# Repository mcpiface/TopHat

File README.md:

# TopHat

Pi Top "Hat" to provide blade style power connectivity through from a back plane, with the addition of McPiFace I2C connections, front panel LED connection and some additional functionality.

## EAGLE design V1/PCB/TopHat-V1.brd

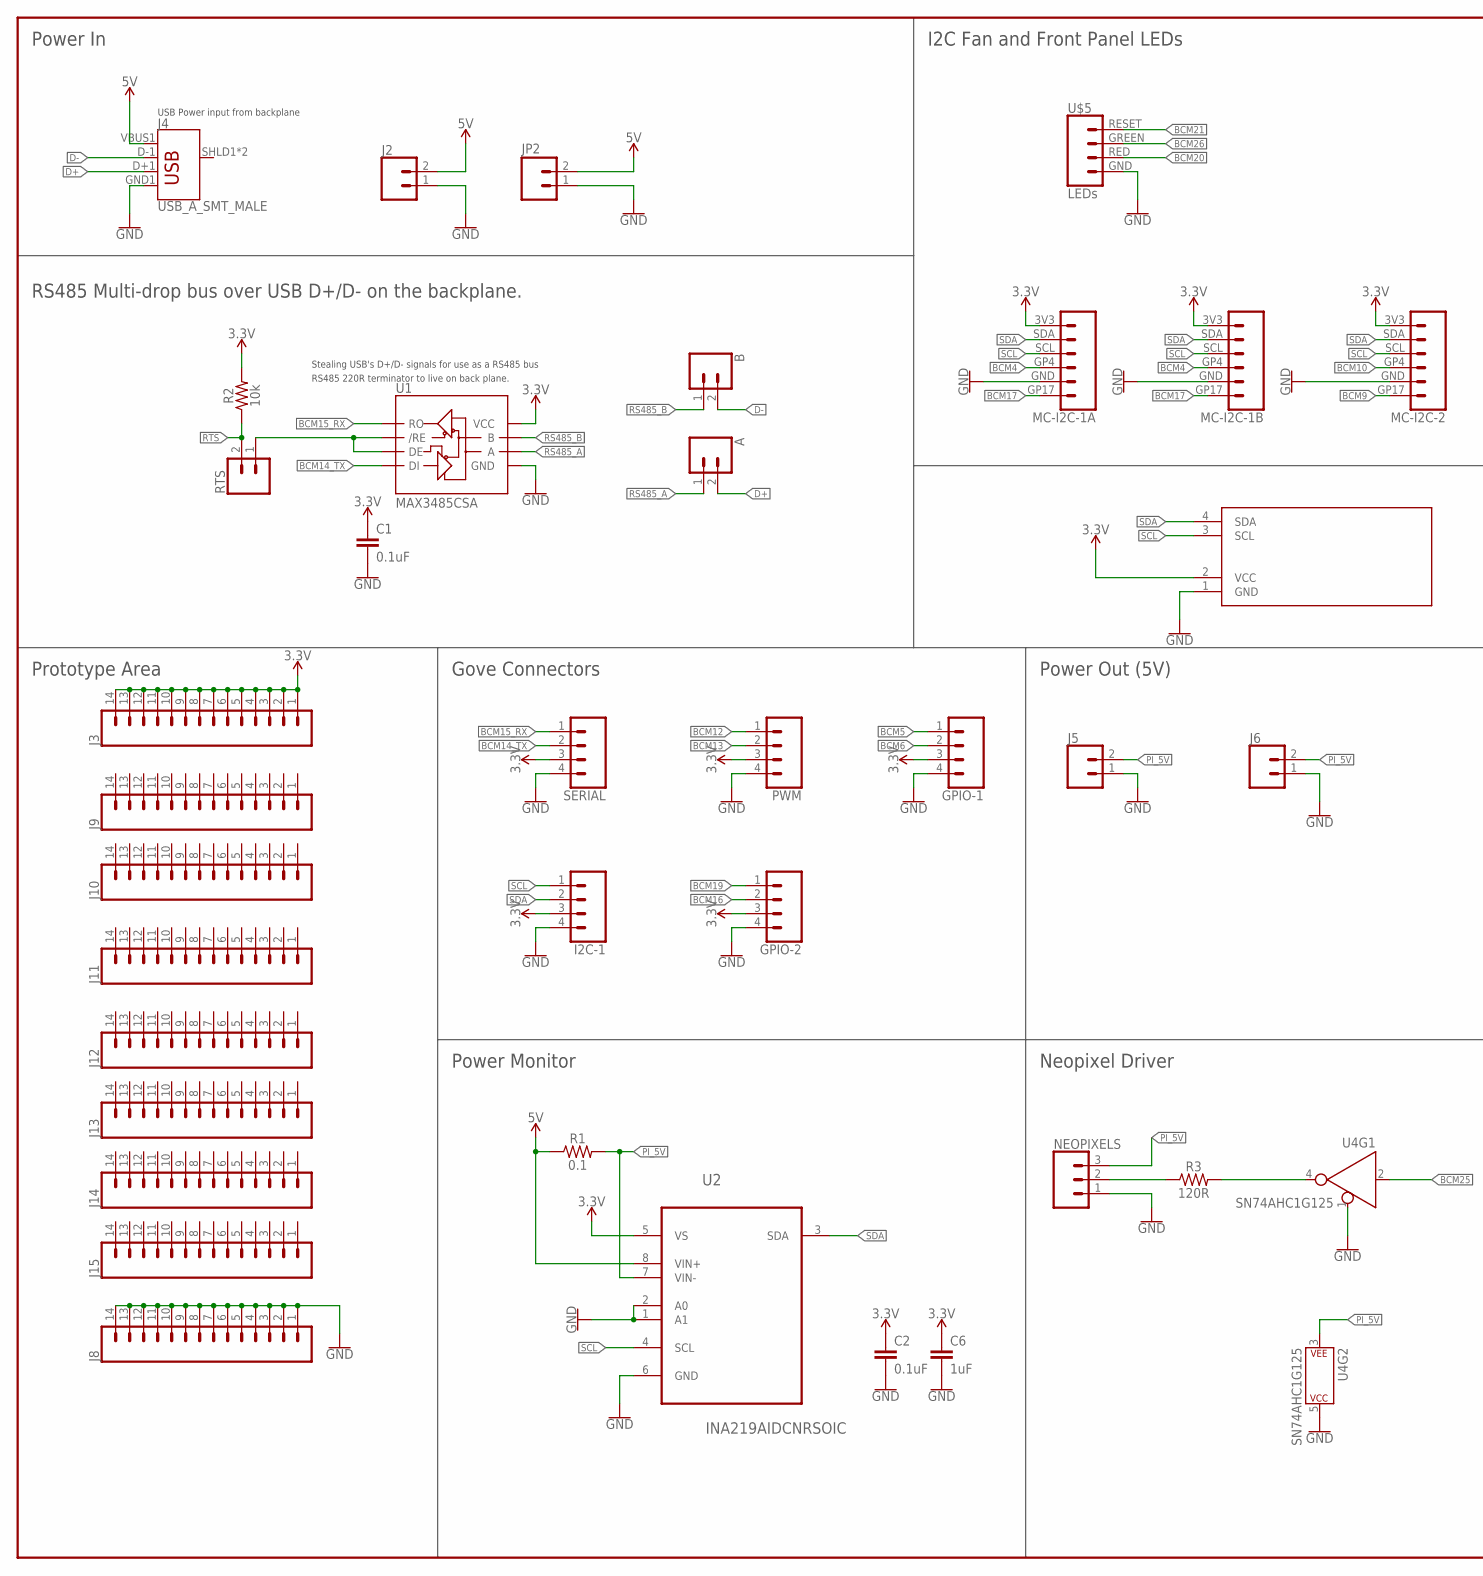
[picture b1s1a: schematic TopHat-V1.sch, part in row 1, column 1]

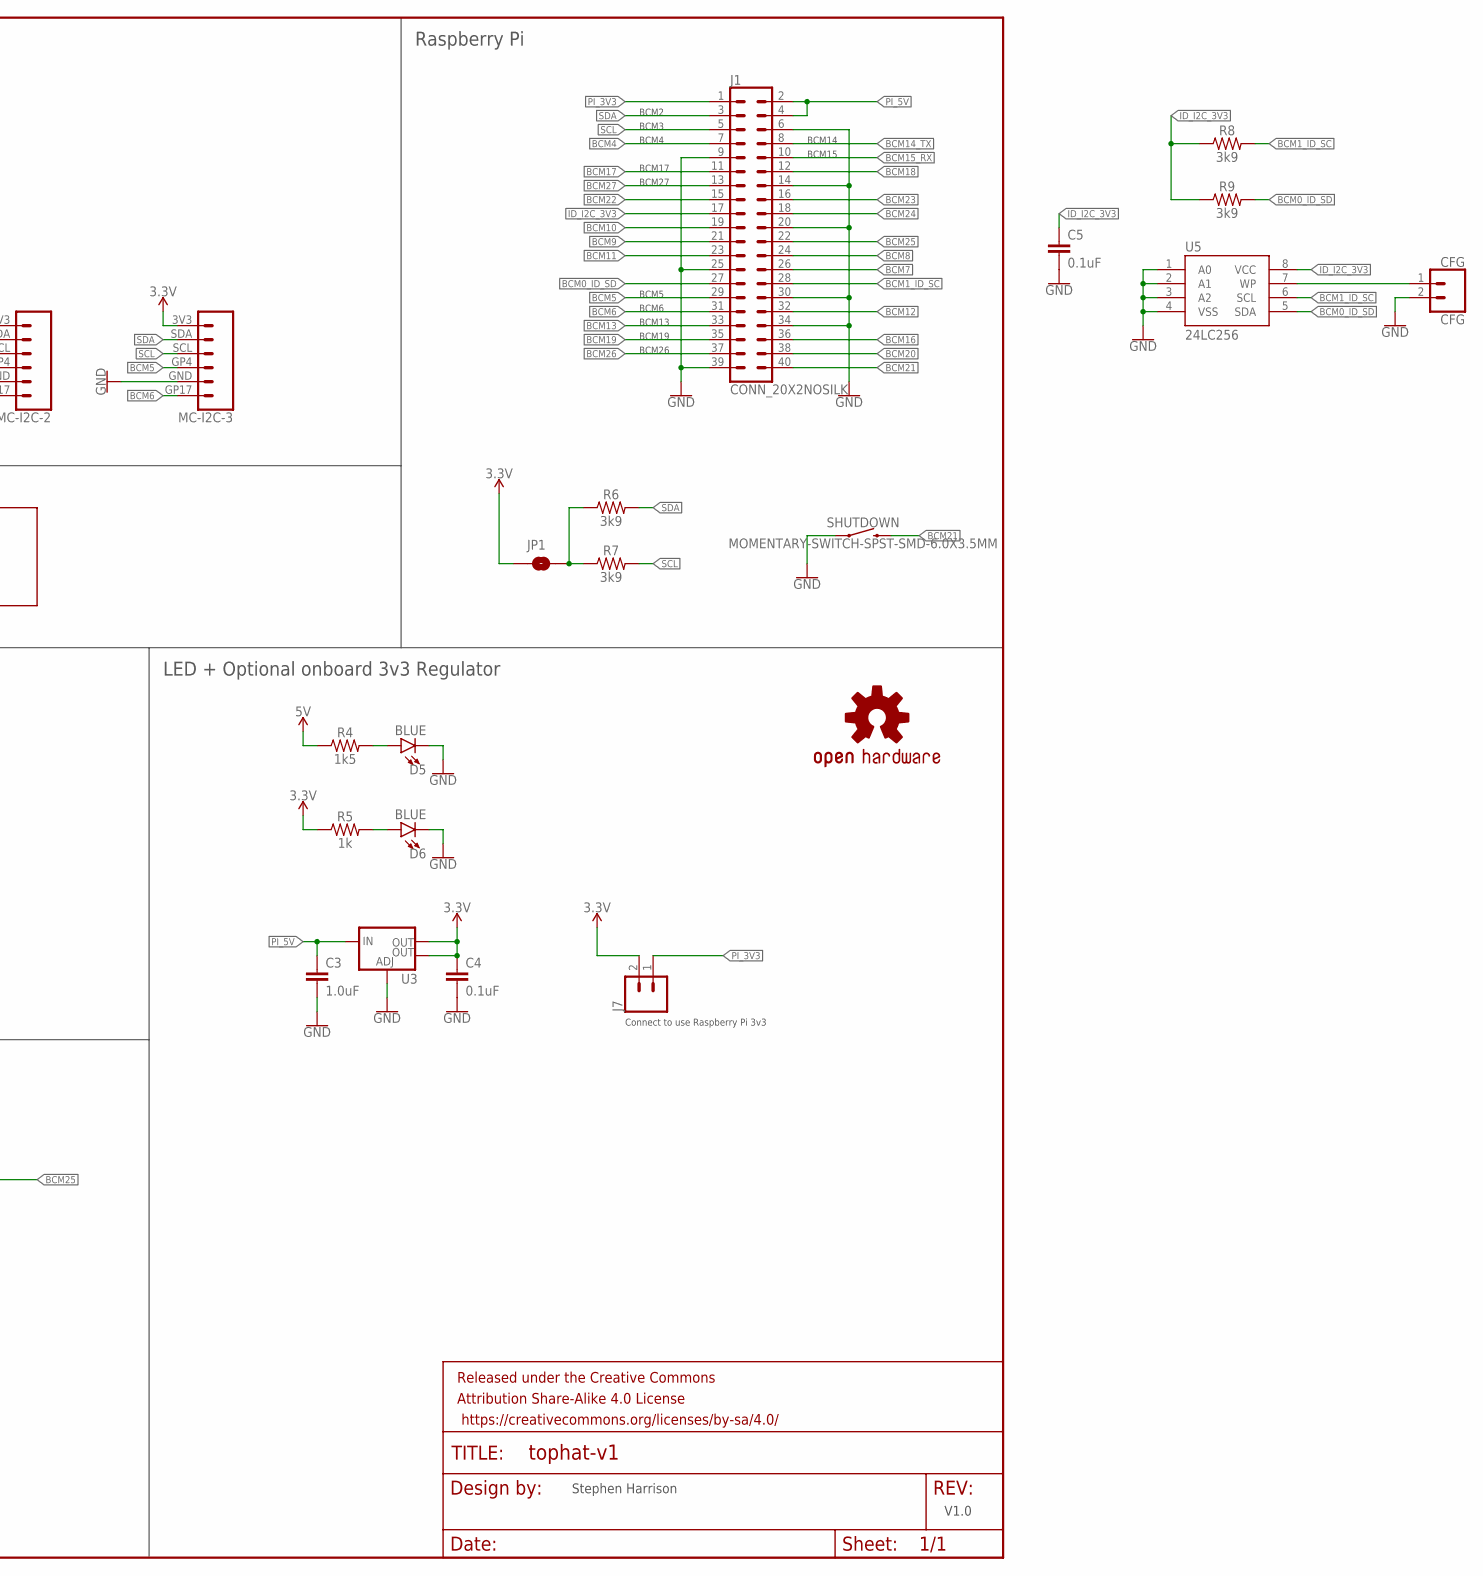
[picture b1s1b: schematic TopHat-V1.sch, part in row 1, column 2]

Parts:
A: CONN_02; 1X02
B: CONN_02; 1X02
C1, C2, C4, C5: 0.1uF; 0805
C3: 1.0uF; 0805
C6: 1uF; 0805
CFG: CFG; 1X02
D5, D6: BLUE; LED-1206
DISPLAY: DISPLAY0.91_INCH_DISPLAY; I2C_DISPLAY_0.91_INCH
FRAME1: FRAME-LEDGER; CREATIVE_COMMONS
GPIO-1, GPIO-2: CONN_04GROVE-JST-PH-4-2MM; JST-4-PH-GROVE
I2C-1: CONN_04GROVE-JST-PH-4-2MM; JST-4-PH-GROVE
J1: CONN_20X2NOSILK; 2X20_NOSILK
J2, J5, J6: CONN_02POLAR; MOLEX-1X2
J3, J8: CONN_14; 1X14
J4: USB_A_SMT_MALE; USB-A-SMT-MALE
J7: CONN_02; 1X02
J9, J10, J11, J12, J13, J14, J15: CONN_14NO_SILK; 1X14_NO_SILK
JP1: JUMPER-SMT_2_NO_SILK; SMT-JUMPER_2_NO_SILK
JP2: M025MM; SCREWTERMINAL-5MM-2@1
LOGO1: OSHW-LOGOM; OSHW-LOGO-M
MC-I2C-1A, MC-I2C-1B, MC-I2C-2, MC-I2C-3: MC_PI_FACE_CONNECTORS_I2CTOP; JST-6-SH-1.0MM-TOP
NEOPIXELS: CONN_03POLAR; MOLEX-1X3
PWM: CONN_04GROVE-JST-PH-4-2MM; JST-4-PH-GROVE
R1: 0.1; 1210
R2: 10k; 0805
R3: 120R; 0805
R4: 1k5; 0805
R5: 1k; 0805
R6, R7, R8, R9: 3k9; 0805
RTS: CONN_02; 1X02
SERIAL: CONN_04GROVE-JST-PH-4-2MM; JST-4-PH-GROVE
SHUTDOWN: MOMENTARY-SWITCH-SPST-SMD-6.0X3.5MM; TACTILE_SWITCH_SMD_6.0X3.5MM
U1: MAX3485CSA; SO08
U2: INA219AIDCNRSOIC; SO08
U3: V_REG_LM1117SOT223; SOT223
U4: SN74AHC1G125; SOT23-5
U5: 24LC256; SO08
U$1: THINGYSTICKS_LOGO
U$5: LEDs; JST-4-SH-1.0MM-SIDE

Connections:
3.3V: C1.1, C2.1, C4.1, C6.1, DISPLAY.2 (VCC), GPIO-1.3, GPIO-2.3, I2C-1.3, J3.1, J3.2, J3.3, J3.4, J3.5, J3.6, J3.7, J3.8, J3.9, J3.10, J3.11, J3.12, J3.13, J3.14, J7.2, JP1.1, MC-I2C-1A.3V3, MC-I2C-1B.3V3, MC-I2C-2.3V3, MC-I2C-3.3V3, PWM.3, R2.2, R5.1, SERIAL.3, U1.8 (VCC), U2.5 (VS), U3.2 (OUT), U3.4 (OUT)
5V: J2.2, J4.VBUS1 (VBUS), JP2.2, R1.1, R4.1, U2.8 (VIN+)
BCM0_ID_SD: J1.27, R9.2, U5.5 (SDA)
BCM1_ID_SC: J1.28, R8.2, U5.6 (SCL)
BCM4: J1.7, MC-I2C-1A.GP4, MC-I2C-1B.GP4
BCM5: GPIO-1.1, J1.29, MC-I2C-3.GP4
BCM6: GPIO-1.2, J1.31, MC-I2C-3.GP17
BCM7: J1.26
BCM8: J1.24
BCM9: J1.21, MC-I2C-2.GP17
BCM10: J1.19, MC-I2C-2.GP4
BCM11: J1.23
BCM12: J1.32, PWM.1
BCM13: J1.33, PWM.2
BCM14_TX: J1.8, SERIAL.2, U1.4 (DI)
BCM15_RX: J1.10, SERIAL.1, U1.1 (RO)
BCM16: GPIO-2.2, J1.36
BCM17: J1.11, MC-I2C-1A.GP17, MC-I2C-1B.GP17
BCM18: J1.12
BCM19: GPIO-2.1, J1.35
BCM20: J1.38, U$5.RED
BCM21: J1.40, SHUTDOWN.2, U$5.RESET
BCM22: J1.15
BCM23: J1.16
BCM24: J1.18
BCM25: J1.22, U4.2 (A)
BCM26: J1.37, U$5.GREEN
BCM27: J1.13
D+: A.2, J4.D+1 (D+)
D-: B.2, J4.D-1 (D-)
GND: C1.2, C2.2, C3.2, C4.2, C5.2, C6.2, CFG.2, D5.C, D6.C, DISPLAY.1 (GND), GPIO-1.4, GPIO-2.4, I2C-1.4, J1.6, J1.9, J1.14, J1.20, J1.25, J1.30, J1.34, J1.39, J2.1, J4.GND1 (GND), J5.1, J6.1, J8.1, J8.2, J8.3, J8.4, J8.5, J8.6, J8.7, J8.8, J8.9, J8.10, J8.11, J8.12, J8.13, J8.14, JP2.1, MC-I2C-1A.GND, MC-I2C-1B.GND, MC-I2C-2.GND, MC-I2C-3.GND, NEOPIXELS.1, PWM.4, SERIAL.4, SHUTDOWN.1, U1.5 (GND), U2.1 (A1), U2.2 (A0), U2.6 (GND), U3.1 (ADJ), U4.1 (!EN), U4.5 (P$V+), U5.1 (A0), U5.2 (A1), U5.3 (A2), U5.4 (VSS), U$5.GND
ID_I2C_3V3: C5.1, J1.17, R8.1, R9.1, U5.8 (VCC)
unnamed: CFG.1, U5.7 (WP)
unnamed: D6.A, R5.2
unnamed: D5.A, R4.2
unnamed: RTS.1, U1.2 (/RE), U1.3 (DE)
unnamed: JP1.2, R6.1, R7.1
unnamed: NEOPIXELS.2, R3.1
unnamed: R3.2, U4.4 (Y)
PI_3V3: J1.1, J7.1
PI_5V: C3.1, J1.2, J1.4, J5.2, J6.2, NEOPIXELS.3, R1.2, U2.7 (VIN-), U3.3 (IN), U4.3 (P$V-)
RS485_A: A.1, U1.6 (A)
RS485_B: B.1, U1.7 (B)
RTS: R2.1, RTS.2
SCL: DISPLAY.3 (SCL), I2C-1.1, J1.5, MC-I2C-1A.SCL, MC-I2C-1B.SCL, MC-I2C-2.SCL, MC-I2C-3.SCL, R7.2, U2.4 (SCL)
SDA: DISPLAY.4 (SDA), I2C-1.2, J1.3, MC-I2C-1A.SDA, MC-I2C-1B.SDA, MC-I2C-2.SDA, MC-I2C-3.SDA, R6.2, U2.3 (SDA)

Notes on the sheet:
BCM13
BCM6
BCM5
BCM26
BCM19
Stealing USB's D+/D- signals for use as a RS485 bus
RS485 220R terminator to live on back plane.
Connect to use Raspberry Pi 3v3
USB Power input from backplane
BCM14
BCM15
BCM2
BCM3
BCM4
BCM17
BCM27
Power In
RS485 Multi-drop bus over USB D+/D- on the backplane.
Raspberry Pi
Prototype Area
Gove Connectors
LED + Optional onboard 3v3 Regulator
I2C Fan and Front Panel LEDs
Neopixel Driver
Power Monitor
Power Out (5V)
Stephen Harrison
V1.0

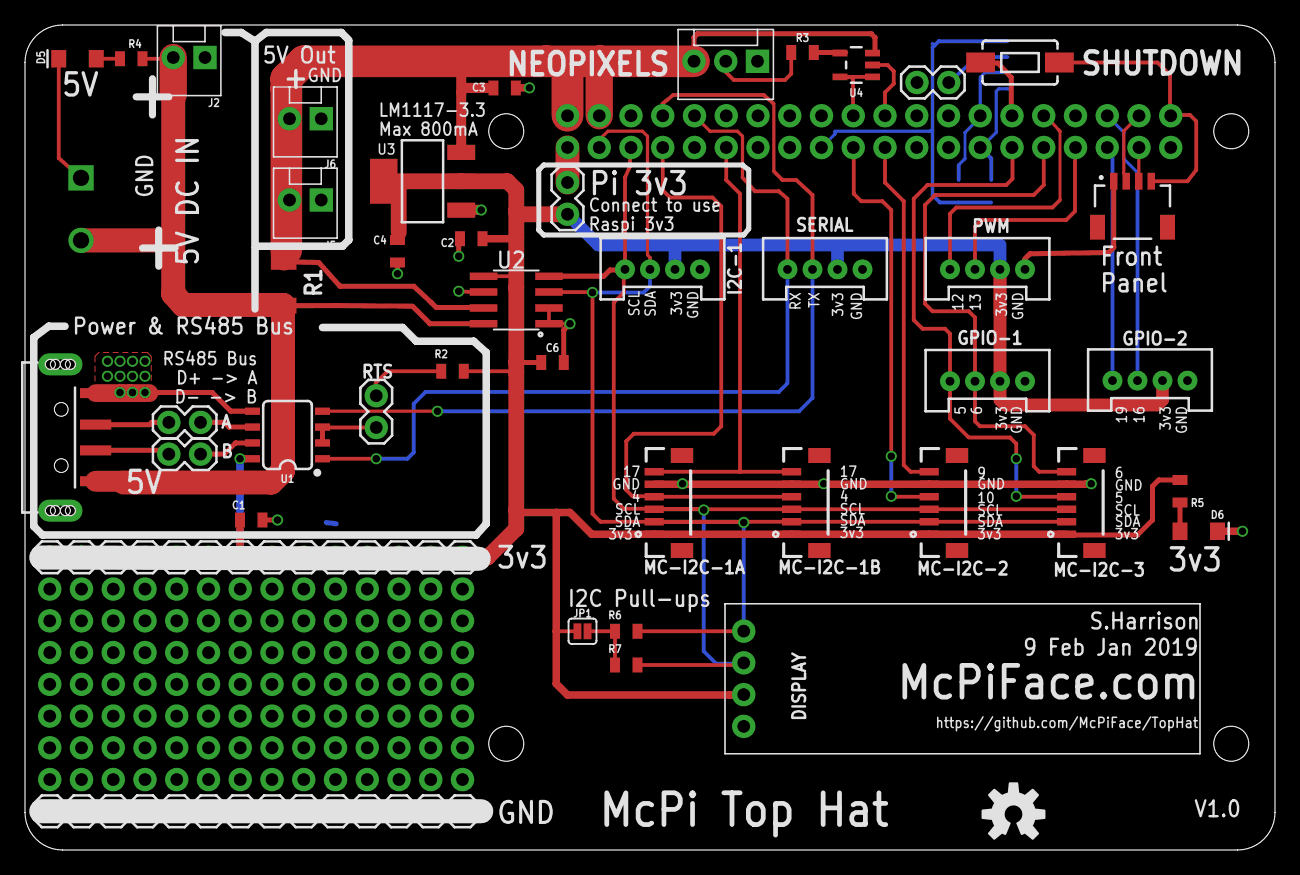
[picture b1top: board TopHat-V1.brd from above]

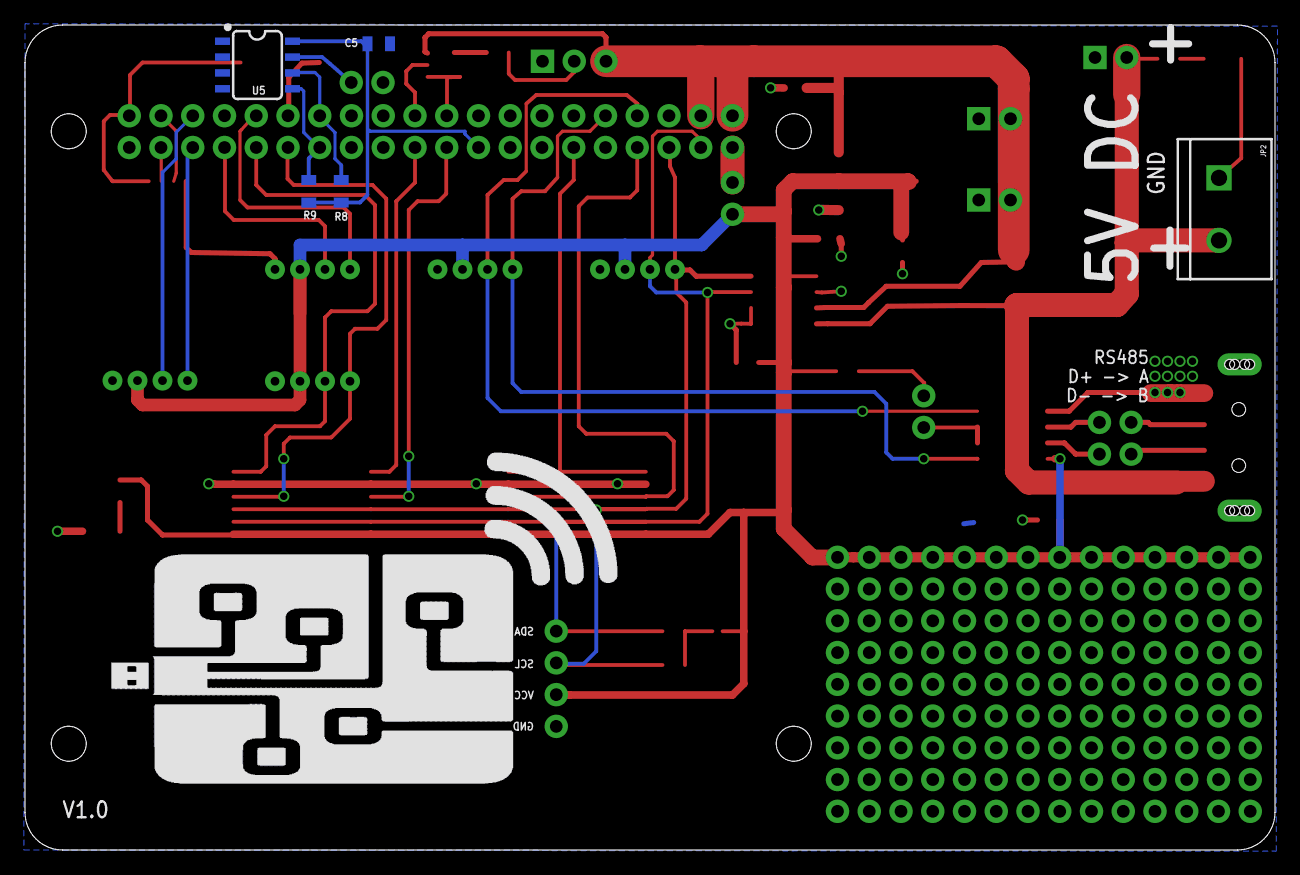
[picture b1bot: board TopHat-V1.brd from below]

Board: 2 copper layers, 100.0 x 66.0 mm, 59 parts (7 on the bottom side), 38 nets.

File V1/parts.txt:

Partlist

Exported from TopHat-V1.brd at 09/02/2019 21:39

EAGLE Version 7.4.0 Copyright (c) 1988-2015 CadSoft

Assembly variant: 

Part      Value                               Package                      Library             Position (inch)       Orientation

A                                             1X02                         SparkFun-Connectors (-0.825 1.15)         R180
B                                             1X02                         SparkFun-Connectors (-0.825 1.05)         R180
C1        0.1uF                               0805                         SparkFun-Capacitors (-0.66535433 0.84251969) R0
C2        0.1uF                               0805                         SparkFun-Capacitors (0.02755906 1.72834646) R180
C3        1.0uF                               0805                         SparkFun-Capacitors (0.13267717 2.20334646) R0
C4        0.1uF                               0805                         SparkFun-Capacitors (-0.20472441 1.68897638) R270
C5        0.1uF                               0805                         SparkFun-Capacitors (1.44488189 2.34251969) MR0
C6        1uF                                 0805                         SparkFun-Capacitors (0.28346457 1.33858268) R0
CFG       CFG                                 1X02                         SparkFun-Connectors (1.53149606 2.22047244) R180
D5        BLUE                                LED-1206                     SparkFun-LED        (-1.21259843 2.29527559) R180
D6        BLUE                                LED-1206                     SparkFun-LED        (2.31889764 0.80708661) R0
DISPLAY   DISPLAY0.91_INCH_DISPLAY            I2C_DISPLAY_0.91_INCH        ThingySticks        (0.82677165 0.10629921) R0
GPIO-1                                        JST-4-PH-GROVE               ThingySticks        (1.65354331 1.3011811) R0
GPIO-2                                        JST-4-PH-GROVE               ThingySticks        (2.16535433 1.30314961) R0
I2C-1                                         JST-4-PH-GROVE               ThingySticks        (0.62992126 1.65354331) R0
J1        CONN_20X2NOSILK                     2X20_NOSILK                  SparkFun-Connectors (0.33070866 2.01574803) R0
J2                                            MOLEX-1X2                    SparkFun-Connectors (-0.81102362 2.2992126) R180
J3                                            1X14                         SparkFun-Connectors (-1.3 0.725)          R0
J4        USB_A_SMT_MALE                      USB-A-SMT-MALE               Tinamous            (-1.58661417 1.1023622) R0
J5                                            MOLEX-1X2                    SparkFun-Connectors (-0.44488189 1.8503937) R180
J6                                            MOLEX-1X2                    SparkFun-Connectors (-0.44488189 2.10629921) R180
J7                                            1X02                         SparkFun-Connectors (0.33070866 1.90551181) R270
J8                                            1X14                         SparkFun-Connectors (-1.3 -0.075)         R0
J9                                            1X14_NO_SILK                 SparkFun-Connectors (-1.3 0.625)          R0
J10                                           1X14_NO_SILK                 SparkFun-Connectors (-1.3 0.525)          R0
J11                                           1X14_NO_SILK                 SparkFun-Connectors (-1.3 0.425)          R0
J12                                           1X14_NO_SILK                 SparkFun-Connectors (-1.3 0.325)          R0
J13                                           1X14_NO_SILK                 SparkFun-Connectors (-1.3 0.225)          R0
J14                                           1X14_NO_SILK                 SparkFun-Connectors (-1.3 0.125)          R0
J15                                           1X14_NO_SILK                 SparkFun-Connectors (-1.3 0.025)          R0
JP1       JUMPER-SMT_2_NO_SILK                SMT-JUMPER_2_NO_SILK         SparkFun-Jumpers    (0.37795276 0.49212598) R0
JP2                                           SCREWTERMINAL-5MM-2@1        SparkFun-Connectors (-1.2015748 1.92007874) MR270
MC-I2C-1A MC_PI_FACE_CONNECTORS_I2CTOP        JST-6-SH-1.0MM-TOP           McPiFace            (0.65354331 0.8976378) R90
MC-I2C-1B MC_PI_FACE_CONNECTORS_I2CTOP        JST-6-SH-1.0MM-TOP           McPiFace            (1.08661417 0.8976378) R90
MC-I2C-2  MC_PI_FACE_CONNECTORS_I2CTOP        JST-6-SH-1.0MM-TOP           McPiFace            (1.51968504 0.8976378) R90
MC-I2C-3  MC_PI_FACE_CONNECTORS_I2CTOP        JST-6-SH-1.0MM-TOP           McPiFace            (1.95275591 0.8976378) R90
NEOPIXELS                                     MOLEX-1X3                    SparkFun-Connectors (0.92913386 2.28740157) R180
PWM                                           JST-4-PH-GROVE               ThingySticks        (1.65354331 1.65354331) R0
R1        0.1                                 1210                         SparkFun-Resistors  (-0.56299213 1.58661417) R90
R2        10k                                 0805                         SparkFun-Resistors  (-0.03149606 1.31102362) R0
R3        120R                                0805                         SparkFun-Resistors  (1.07086614 2.31496063) R0
R4        1k5                                 0805                         SparkFun-Resistors  (-1.04330709 2.29527559) R180
R5        1k                                  0805                         SparkFun-Resistors  (2.25984252 0.93307087) R270
R6        3k9                                 0805                         SparkFun-Resistors  (0.51574803 0.49212598) R0
R7        3k9                                 0805                         SparkFun-Resistors  (0.51574803 0.38582677) R0
R8        3k9                                 0805                         SparkFun-Resistors  (1.56299213 1.87795276) MR90
R9        3k9                                 0805                         SparkFun-Resistors  (1.66535433 1.87795276) MR90
RTS                                           1X02                         SparkFun-Connectors (-0.27165354 1.13385827) R90
SERIAL                                        JST-4-PH-GROVE               ThingySticks        (1.14173228 1.65354331) R0
SHUTDOWN  MOMENTARY-SWITCH-SPST-SMD-6.0X3.5MM TACTILE_SWITCH_SMD_6.0X3.5MM ThingySticks        (1.75590551 2.28346457) R0
U$5       LEDs                                JST-4-SH-1.0MM-SIDE          McPiFace            (2.11023622 1.90944882) R0
U1         MAX3485CSA                         SO08                         SparkFun-IC-Comms   (-0.5511811 1.11023622) R90
U2        INA219AIDCNRSOIC                    SO08                         INA219AIDCNR        (0.16929134 1.53543307) R90
U3                                            SOT223                       SparkFun-PowerIC    (-0.12598425 1.90944882) R90
U4        SN74AHC1G125                        SOT23-5                      SparkFun-IC-Logic   (1.24015748 2.27559055) R90
U5        24LC256                             SO08                         SparkFun-IC-Memory  (1.82677165 2.27559055) MR270

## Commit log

2019-02-09 V1 ported across from ThingySticks / PiRack repository
    Updated for McPiFace I2C connectors
    Removed 3 status panel connectors as V2 is I2C
    Added ThingySticks logo
    Added 2x 2 pin Molex 5V supplys for RGB LED panels

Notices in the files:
parts and their libraries:
SparkFun-Connectors: Licensing: Creative Commons ShareAlike 4.0 International - https://creativecommons.org/licenses/by-sa/4.0
SparkFun-Aesthetics: Released under the Creative Commons Attribution Share-Alike 4.0 License
SparkFun-Aesthetics: https://creativecommons.org/licenses/by-sa/4.0
